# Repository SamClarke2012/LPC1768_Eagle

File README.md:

LPC1768_Eagle
=============

A working example. design with MBED, load with flash magic.

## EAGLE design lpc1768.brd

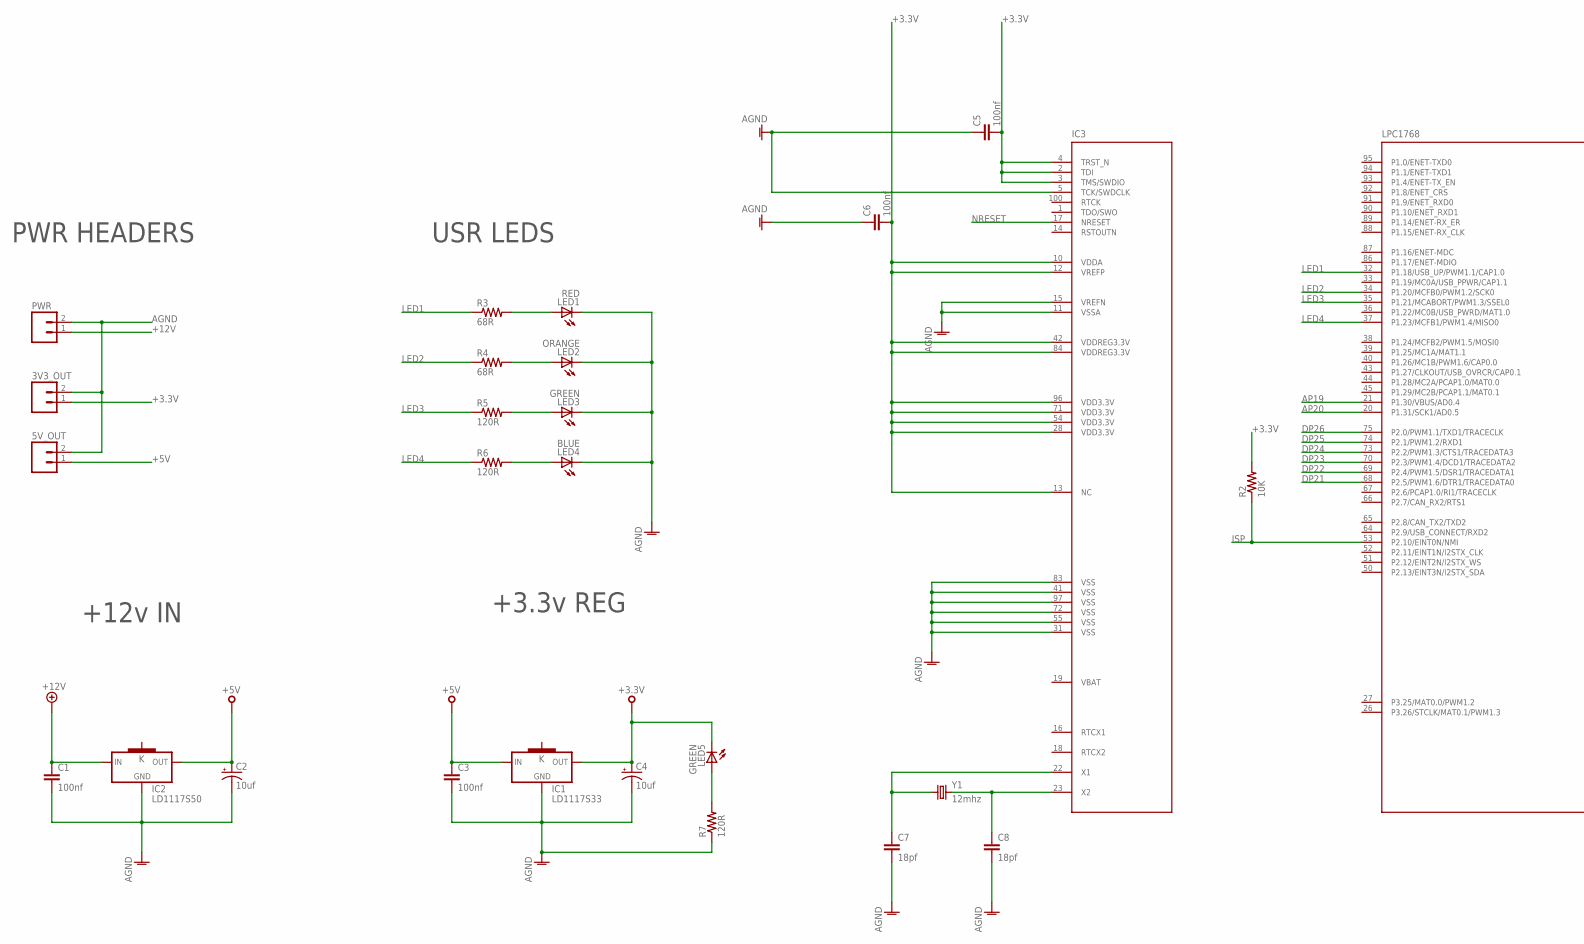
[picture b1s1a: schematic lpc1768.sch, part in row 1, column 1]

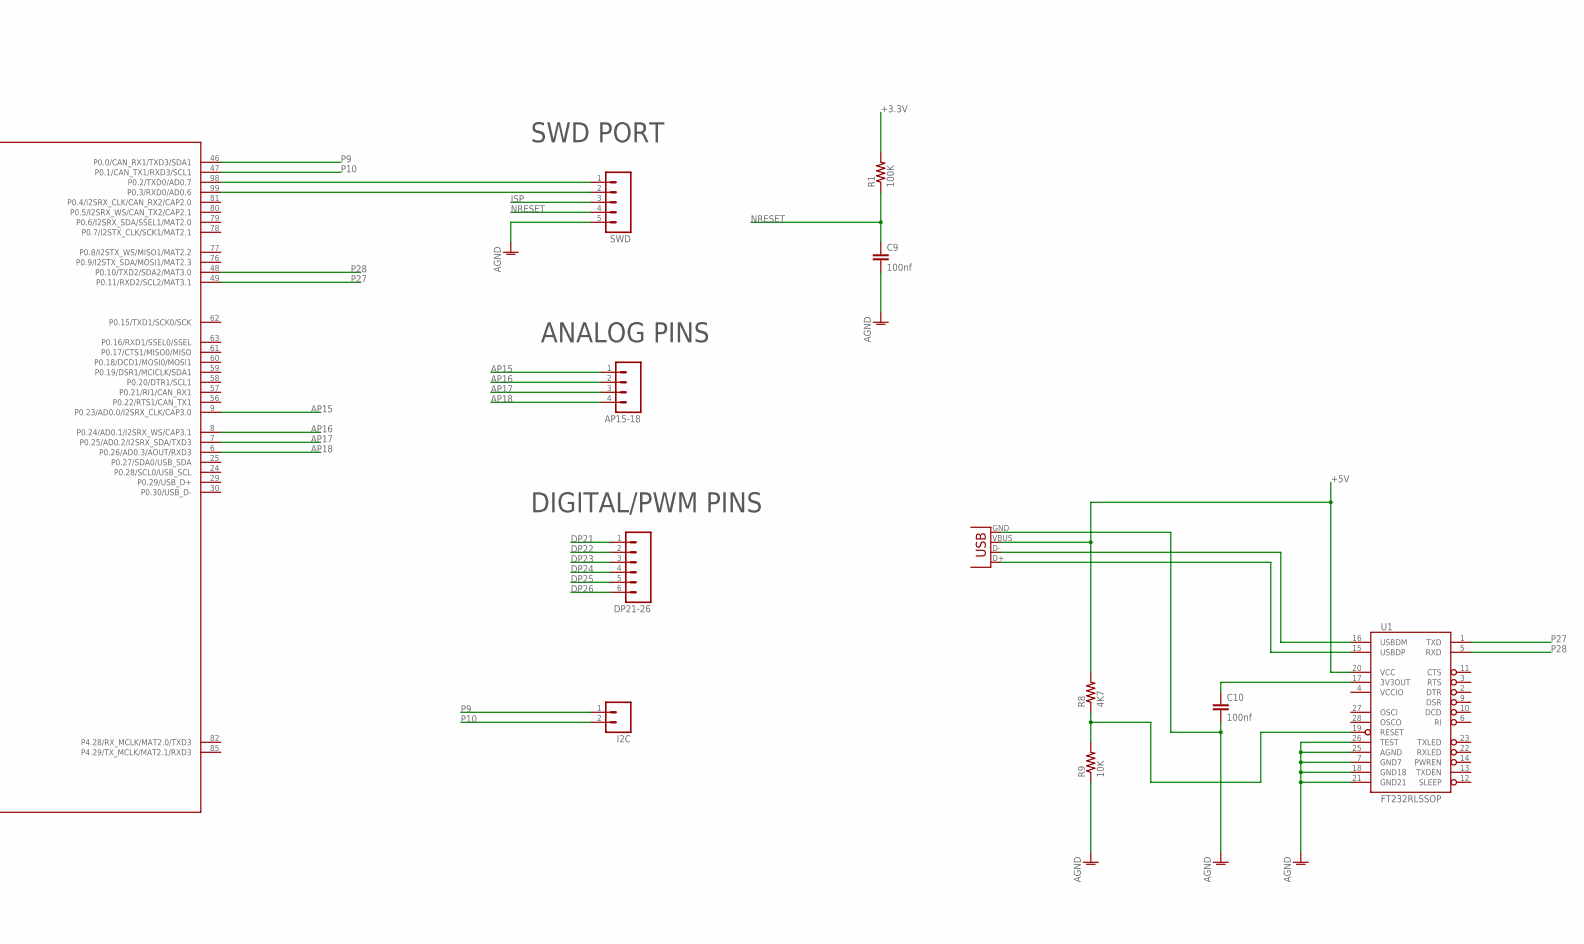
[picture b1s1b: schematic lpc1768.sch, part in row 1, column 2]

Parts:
3V3_OUT, 5V_OUT: M02PTH3; 1X02_LONGPADS
AP15-18: M04LONGPADS; 1X04_LONGPADS
C1, C3, C5, C6, C9, C10: 100nf; 1206
C2, C4: 10uf; EIA3216-KIT
C7, C8: 18pf; 1206
DP21-26: M06LONGPADS; 1X06_LONGPADS
I2C: M02PTH3; 1X02_LONGPADS
IC1: LD1117S33; SOT223
IC2: LD1117S50; SOT223
IC3: LPC1768; LQFP100
LED1: RED; LED-1206
LED2: ORANGE; LED-1206
LED3, LED5: GREEN; LED-1206
LED4: BLUE; LED-1206
PWR: M02PTH3; 1X02_LONGPADS
R1: 100K; 1206
R2, R9: 10K; 1206
R3, R4: 68R; 1206
R5, R6, R7: 120R; 1206
R8: 4K7; 1206
SWD: M05PTH_LONGPADS; 1X05_LONGPADS
U1: FT232RLSSOP; SSOP28DB
X1: USB-MB-S
Y1: 12mhz; CRYSTAL-SMD-5X3

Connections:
+3.3V: 3V3_OUT.1, C4.A (+), C5.2, C6.2, IC1.2 (OUT), IC3.2 (TDI), IC3.3 (TMS/SWDIO), IC3.4 (TRST_N), IC3.10 (VDDA), IC3.12 (VREFP), IC3.13 (NC), IC3.28 (VDD3.3V), IC3.42 (VDDREG3.3V), IC3.54 (VDD3.3V), IC3.71 (VDD3.3V), IC3.84 (VDDREG3.3V), IC3.96 (VDD3.3V), LED5.C, R1.2, R2.2
+5V: 5V_OUT.1, C2.A (+), C3.1, IC1.3 (IN), IC2.2 (OUT), R8.2, U1.20 (VCC), X1.VBUS
+12V: C1.1, IC2.3 (IN), PWR.1
AGND: 3V3_OUT.2, 5V_OUT.2, C1.2, C2.C (-), C3.2, C4.C (-), C5.1, C6.1, C7.2, C8.2, C9.2, C10.2, IC1.1 (GND), IC2.1 (GND), IC3.5 (TCK/SWDCLK), IC3.11 (VSSA), IC3.15 (VREFN), IC3.31 (VSS), IC3.41 (VSS), IC3.55 (VSS), IC3.72 (VSS), IC3.83 (VSS), IC3.97 (VSS), LED1.C, LED2.C, LED3.C, LED4.C, PWR.2, R7.1, R9.1, SWD.5, U1.7 (GND7), U1.18 (GND18), U1.21 (GND21), U1.25 (AGND), U1.26 (TEST), X1.GND
AP15: AP15-18.1, IC3.9 (P0.23/AD0.0/I2SRX_CLK/CAP3.0)
AP16: AP15-18.2, IC3.8 (P0.24/AD0.1/I2SRX_WS/CAP3.1)
AP17: AP15-18.3, IC3.7 (P0.25/AD0.2/I2SRX_SDA/TXD3)
AP18: AP15-18.4, IC3.6 (P0.26/AD0.3/AOUT/RXD3)
AP19: IC3.21 (P1.30/VBUS/AD0.4)
AP20: IC3.20 (P1.31/SCK1/AD0.5)
DP21: DP21-26.1, IC3.68 (P2.5/PWM1.6/DTR1/TRACEDATA0)
DP22: DP21-26.2, IC3.69 (P2.4/PWM1.5/DSR1/TRACEDATA1)
DP23: DP21-26.3, IC3.70 (P2.3/PWM1.4/DCD1/TRACEDATA2)
DP24: DP21-26.4, IC3.73 (P2.2/PWM1.3/CTS1/TRACEDATA3)
DP25: DP21-26.5, IC3.74 (P2.1/PWM1.2/RXD1)
DP26: DP21-26.6, IC3.75 (P2.0/PWM1.1/TXD1/TRACECLK)
ISP: IC3.53 (P2.10/EINT0N/NMI), R2.1, SWD.3
LED1: IC3.32 (P1.18/USB_UP/PWM1.1/CAP1.0), R3.1
LED2: IC3.34 (P1.20/MCFB0/PWM1.2/SCK0), R4.1
LED3: IC3.35 (P1.21/MCABORT/PWM1.3/SSEL0), R5.1
LED4: IC3.37 (P1.23/MCFB1/PWM1.4/MISO0), R6.1
unnamed: C8.1, IC3.23 (X2), Y1.3 (2)
unnamed: C7.1, IC3.22 (X1), Y1.1
unnamed: IC3.98 (P0.2/TXD0/AD0.7), SWD.1
unnamed: IC3.99 (P0.3/RXD0/AD0.6), SWD.2
unnamed: LED1.A, R3.2
unnamed: LED2.A, R4.2
unnamed: LED3.A, R5.2
unnamed: LED4.A, R6.2
unnamed: LED5.A, R7.2
unnamed: U1.15 (USBDP), X1.D+
unnamed: U1.16 (USBDM), X1.D-
unnamed: C10.1, U1.17 (3V3OUT)
unnamed: R8.1, R9.2, U1.19 (RESET)
NRESET: C9.1, IC3.17 (NRESET), R1.1, SWD.4
P9: I2C.1, IC3.46 (P0.0/CAN_RX1/TXD3/SDA1)
P10: I2C.2, IC3.47 (P0.1/CAN_TX1/RXD3/SCL1)
P27: IC3.49 (P0.11/RXD2/SCL2/MAT3.1), U1.1 (TXD)
P28: IC3.48 (P0.10/TXD2/SDA2/MAT3.0), U1.5 (RXD)
VCCIO: U1.4 (VCCIO)

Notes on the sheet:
+12v IN
+3.3v REG
PWR HEADERS
USR LEDS
SWD PORT
ANALOG PINS
DIGITAL/PWM PINS

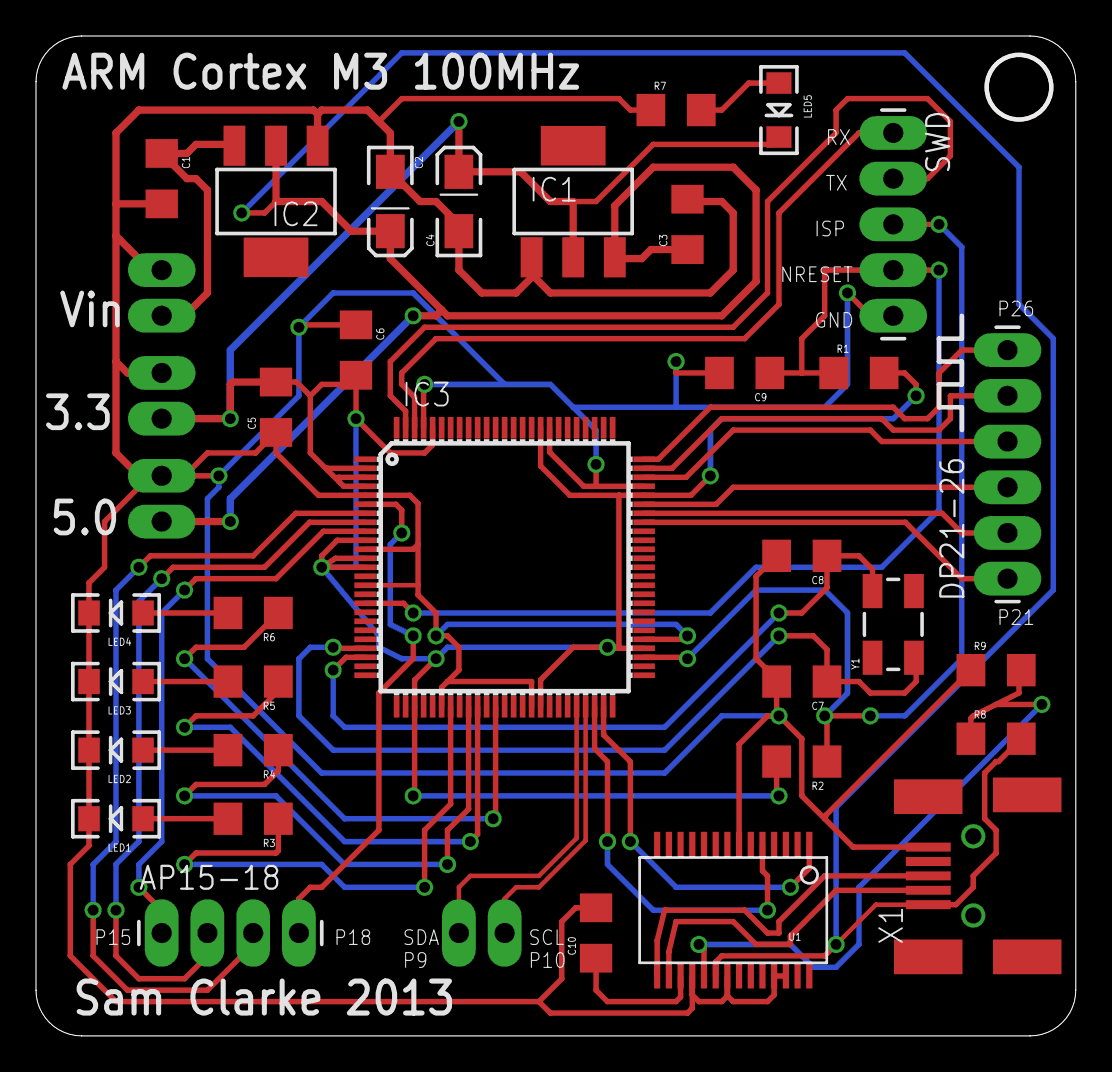
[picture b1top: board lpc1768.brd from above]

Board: 2 copper layers, 57.5 x 55.3 mm, 37 parts (0 on the bottom side), 37 nets.

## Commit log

2014-10-11 init

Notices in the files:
parts and their libraries:
SparkFun-Capacitors: Licensing: CC v3.0 Share-Alike You are welcome to use this library for commercial purposes.
